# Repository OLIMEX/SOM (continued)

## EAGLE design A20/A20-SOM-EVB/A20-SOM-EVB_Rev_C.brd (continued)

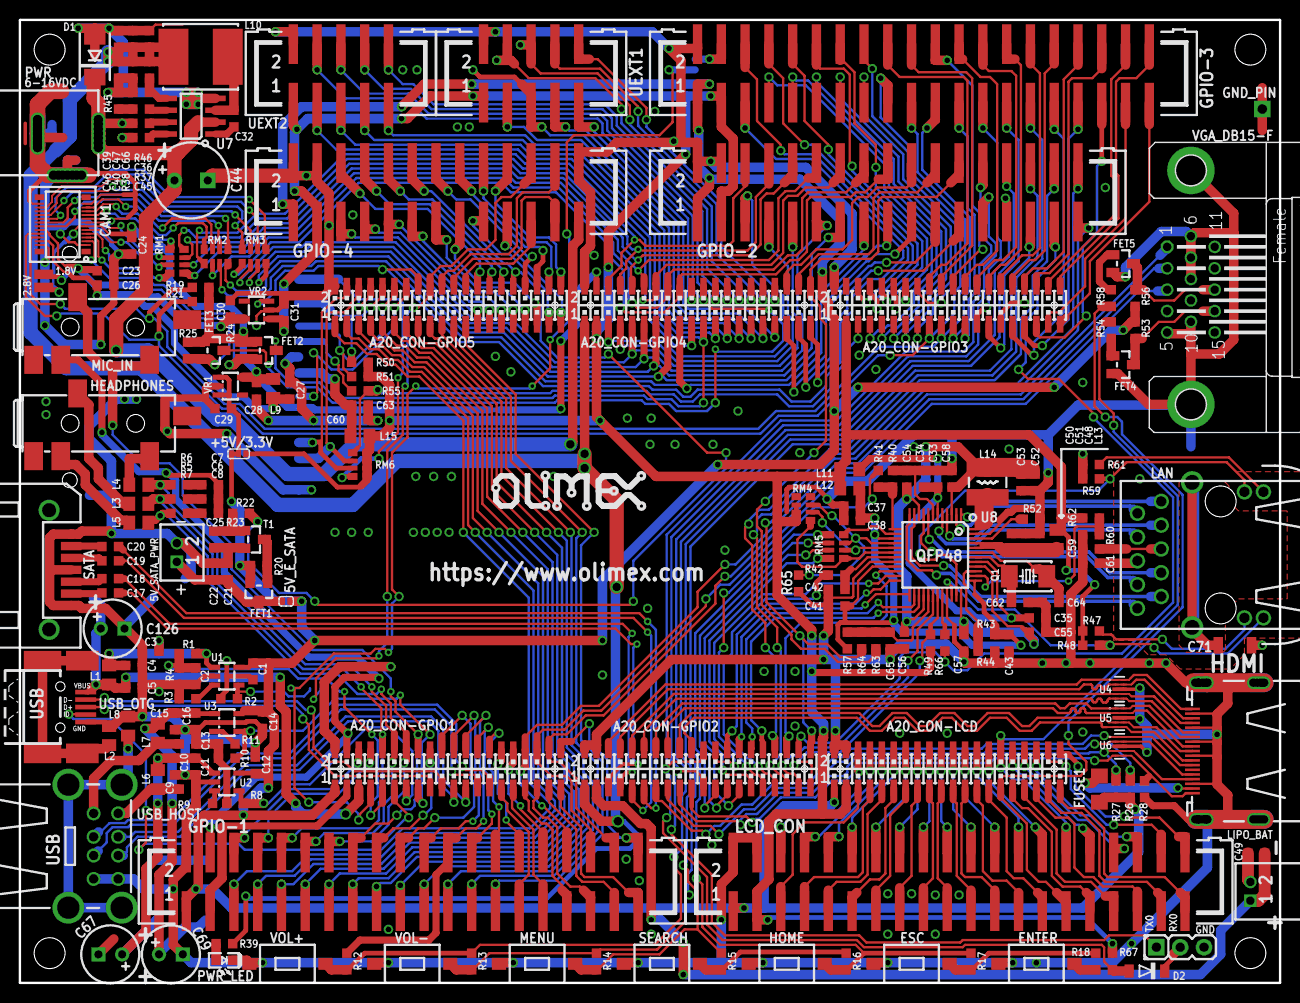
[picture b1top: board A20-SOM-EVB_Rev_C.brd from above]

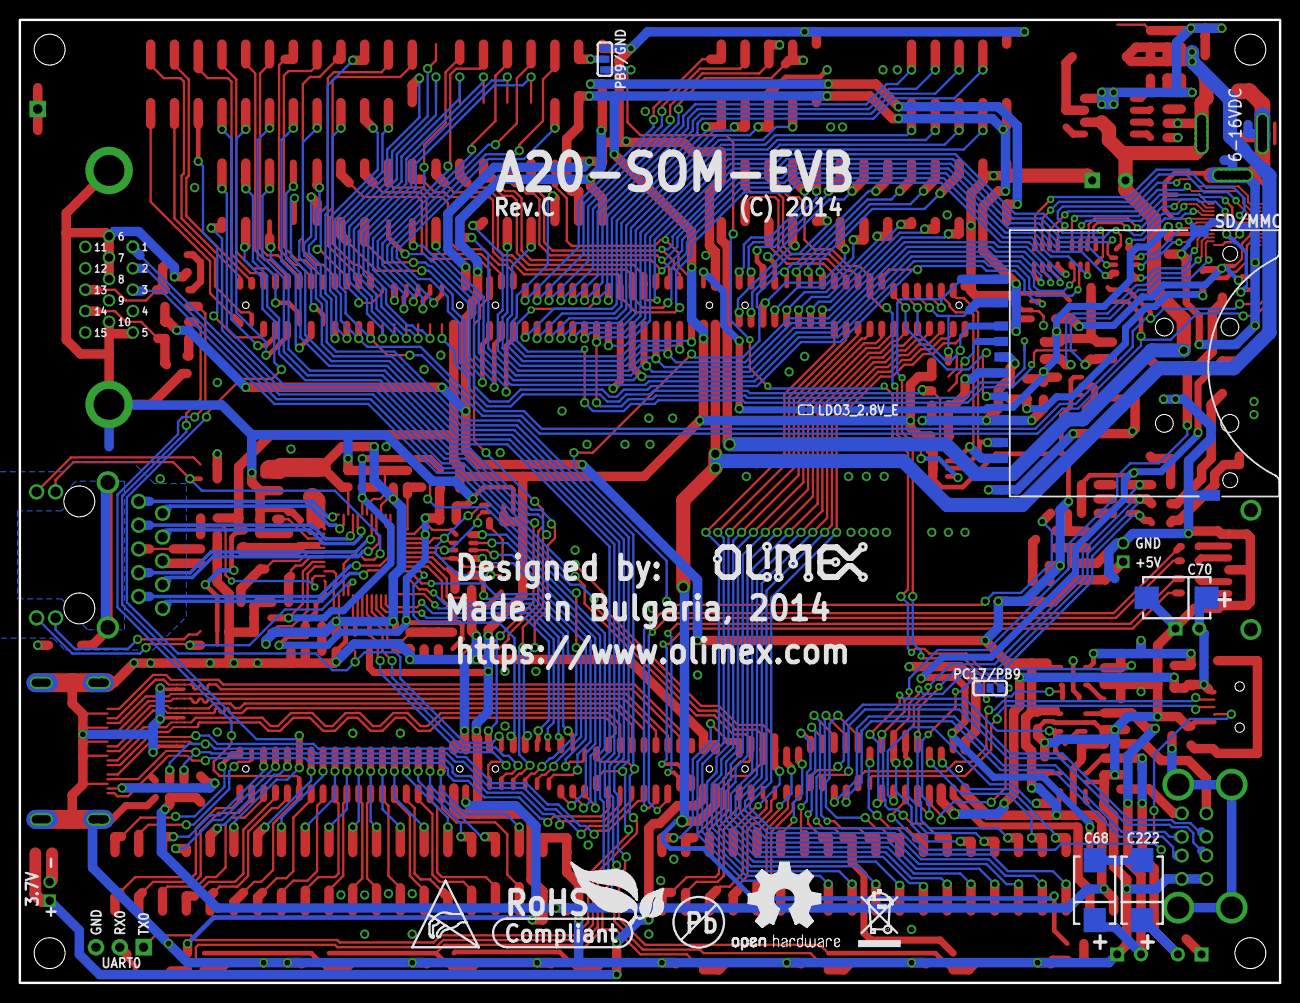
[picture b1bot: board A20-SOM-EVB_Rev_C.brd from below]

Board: 2 copper layers, 134.6 x 102.9 mm, 218 parts (13 on the bottom side), 327 nets.

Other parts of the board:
U$5: LOGO-OPENHARDWARE_8X8
U$6, U$8: OLIMEX1_V
U$9: PB
U$10: ESD_SYMBOL
U$11: RECYCLE_BIN1/8
U$12: ROHS

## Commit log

2014-06-20 init
2014-06-20 A13-SOM files add
2014-06-25 A13-SOM-LTE shield
2014-07-28 Various A20-SOM updates.
2014-10-23 Additional schematics
    Revision B schematics
2014-12-19 Schematics to newer board revisions A20-SOM
2015-02-19 RK3188 SOM files
2015-03-16 Revision C1
2015-03-16 Added files for AM3352
2015-03-16 Updated a number of schematics
2015-05-14 kiCAD connector library
2015-05-15 rk3188 kicad library
2015-05-15 kicad connector templates
2015-10-09 Updated latest schematics
2017-06-22 update
    added schematic for the industrial version of the board, note that it
    doesn't have extra flash memory
2017-10-11 latest hw revision
2018-10-23 Revision changes
2018-11-08 Update
    EEPROM addition was missing from changelog
2019-07-09 Update
    Update changelog
2019-12-18 Update
    Revision G and change log
2020-03-03 Update
    Newer revisions.
2020-06-05 update
    revision changes
2022-06-23 Update
    Revision E files
2022-06-30 Update
    revision E and revision changes
2023-09-07 Update
    Revision F
